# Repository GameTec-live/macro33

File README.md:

# macro33

an attempt at building a small, low profile, portable macro pad...

## Features:

- USB-C
- RP2040 MCU
- QMK
- Hotswap sockets
- Mechanical switches

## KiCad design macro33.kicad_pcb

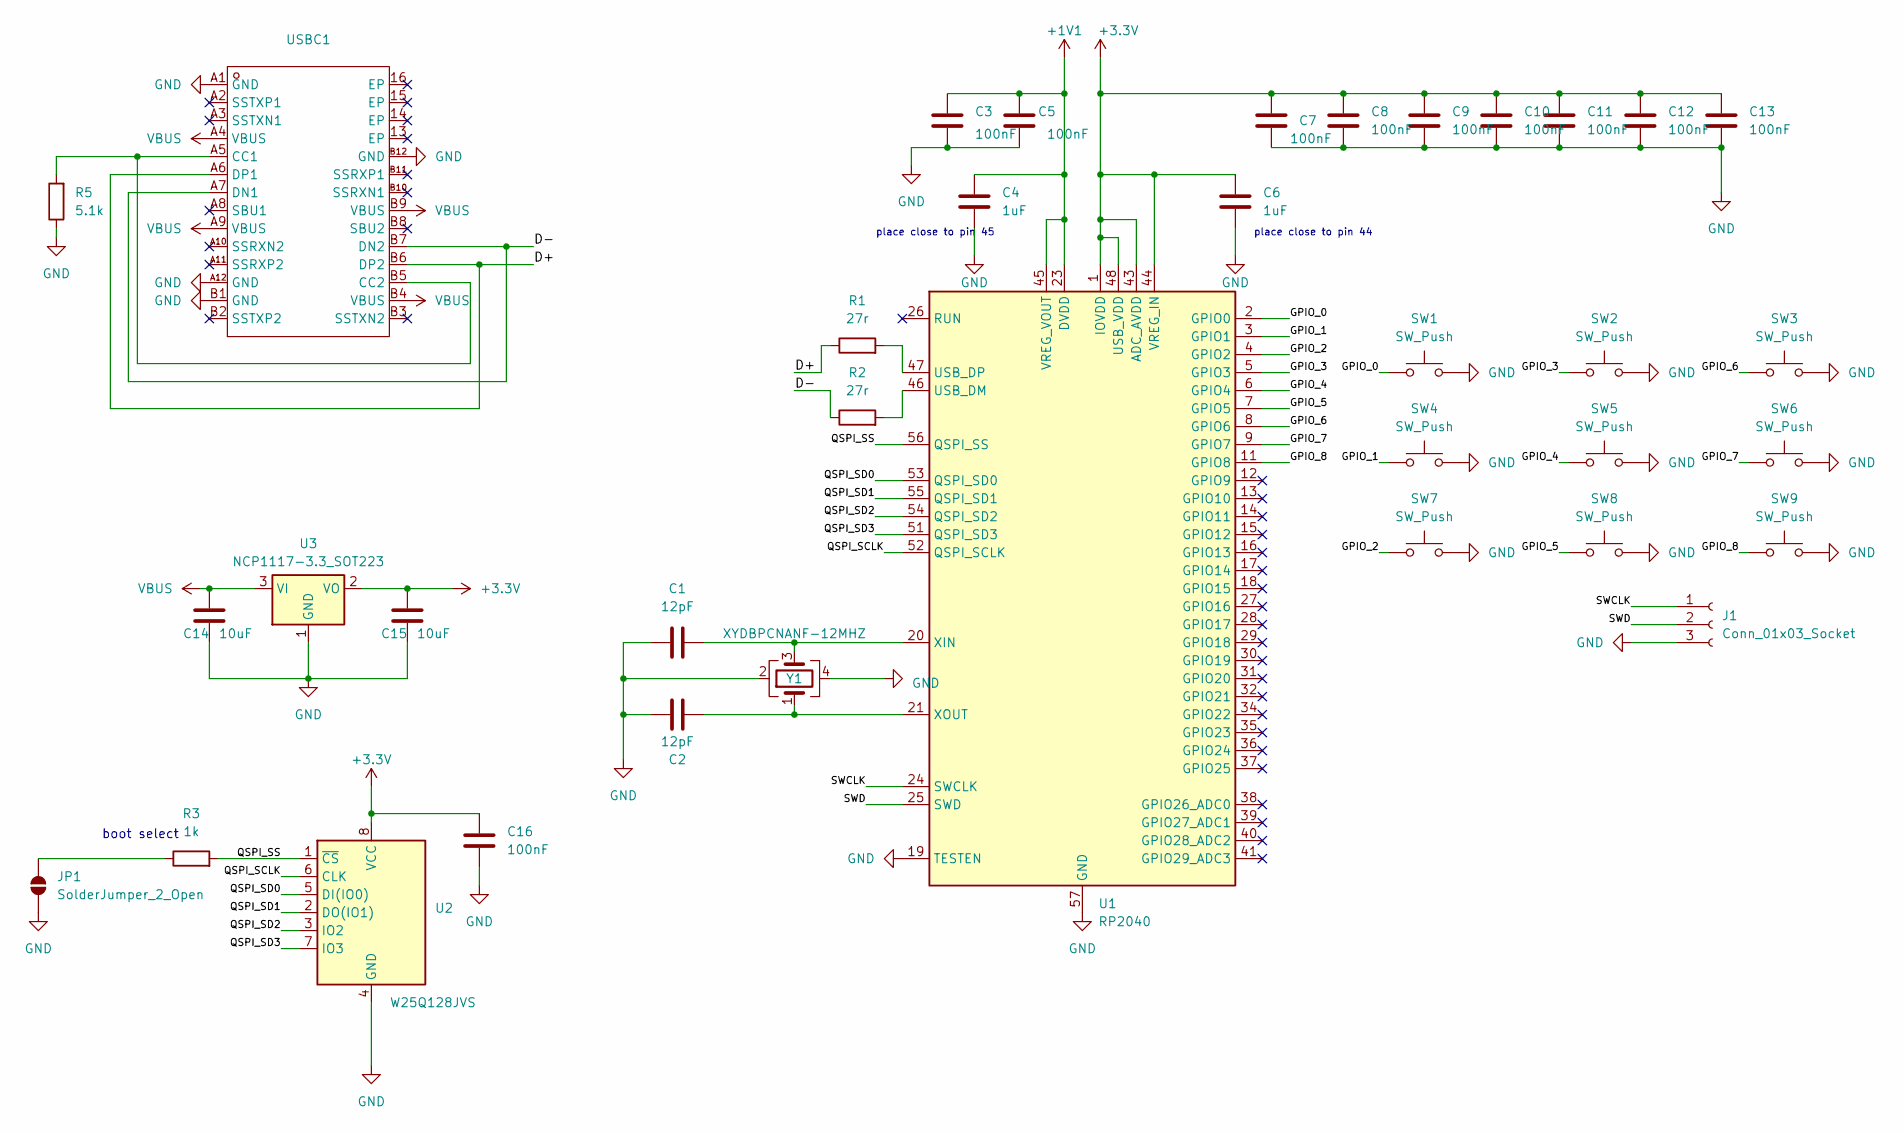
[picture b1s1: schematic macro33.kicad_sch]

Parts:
C1, C2: 12pF; C_0402_1005Metric; LCSC C1547
C3, C5, C7, C8, C9, C10, C11, C12, C13, C16: 100nF; C_0402_1005Metric; LCSC C1525
C4, C6: 1uF; C_0402_1005Metric; LCSC C52923
C14, C15: 10uF; C_1206_3216Metric; LCSC C13585
J1: Conn_01x03_Socket; SWD-Pads
JP1: SolderJumper_2_Open; SolderJumper-2_P1.3mm_Open_TrianglePad1.0x1.5mm
R1, R2: 27r; R_0805_2012Metric; LCSC C17594
R3: 1k; R_0402_1005Metric; LCSC C11702
R5: 5.1k; R_0402_1005Metric; LCSC C25905
SW1, SW2, SW3, SW4, SW5, SW6, SW7, SW8, SW9: SW_Push; CherryMX_MidHeight_Choc_Hotswap_rev5
U1: RP2040; QFN-56-1EP_7x7mm_P0.4mm_EP3.2x3.2mm; LCSC C2040
U2: W25Q128JVS; SOIC-8_5.23x5.23mm_P1.27mm; LCSC C97521
U3: NCP1117-3.3_SOT223; SOT-223-3_TabPin2; LCSC C26537
USBC1: USB-C-SMD_C67380; Manufacturer Part 918-418K2023C40002; LCSC C67380
Y1: XYDBPCNANF-12MHZ; OSC-SMD_4P-L2.5-W2.0-BL; LCSC C521567

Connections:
+1V1: C3.1, C4.1, C5.1, U1.23 (DVDD), U1.45 (VREG_VOUT), U1.50 (DVDD)
+3.3V: C6.1, C7.1, C8.1, C9.1, C10.1, C11.1, C12.1, C13.1, C15.1, C16.1, U1.1 (IOVDD), U1.10 (IOVDD), U1.22 (IOVDD), U1.33 (IOVDD), U1.42 (IOVDD), U1.43 (ADC_AVDD), U1.44 (VREG_IN), U1.48 (USB_VDD), U1.49 (IOVDD), U2.8 (VCC), U3.2 (VO)
/D+: R1.1, USBC1.A6 (DP1), USBC1.B6 (DP2)
/D-: R2.1, USBC1.A7 (DN1), USBC1.B7 (DN2)
/GPIO_0: SW1.1, U1.2 (GPIO0)
/GPIO_1: SW4.1, U1.3 (GPIO1)
/GPIO_2: SW7.1, U1.4 (GPIO2)
/GPIO_3: SW2.1, U1.5 (GPIO3)
/GPIO_4: SW5.1, U1.6 (GPIO4)
/GPIO_5: SW8.1, U1.7 (GPIO5)
/GPIO_6: SW3.1, U1.8 (GPIO6)
/GPIO_7: SW6.1, U1.9 (GPIO7)
/GPIO_8: SW9.1, U1.11 (GPIO8)
/QSPI_SCLK: U1.52 (QSPI_SCLK), U2.6 (CLK)
/QSPI_SD0: U1.53 (QSPI_SD0), U2.5 (DI(IO0))
/QSPI_SD1: U1.55 (QSPI_SD1), U2.2 (DO(IO1))
/QSPI_SD2: U1.54 (QSPI_SD2), U2.3 (IO2)
/QSPI_SD3: U1.51 (QSPI_SD3), U2.7 (IO3)
/QSPI_SS: R3.2, U1.56 (QSPI_SS), U2.1 (~CS)
/SWCLK: J1.1, U1.24 (SWCLK); also elsewhere on the board
/SWD: J1.2, U1.25 (SWD); also elsewhere on the board
GND: C1.1, C2.1, C3.2, C4.2, C5.2, C6.2, C7.2, C8.2, C9.2, C10.2, C11.2, C12.2, C13.2, C14.2, C15.2, C16.2, J1.3, JP1.1 (A), R5.1, SW1.2, SW2.2, SW3.2, SW4.2, SW5.2, SW6.2, SW7.2, SW8.2, SW9.2, U1.19 (TESTEN), U1.57 (GND), U2.4 (GND), U3.1 (GND), USBC1.A1 (GND), USBC1.A12 (GND), USBC1.B1 (GND), USBC1.B12 (GND), Y1.2, Y1.4; also elsewhere on the board
unnamed 22: JP1.2 (B), R3.1; also elsewhere on the board
unnamed: R2.2, U1.46 (USB_DM)
unnamed: R1.2, U1.47 (USB_DP)
unnamed: C1.2, U1.20 (XIN), Y1.3
unnamed: C2.2, U1.21 (XOUT), Y1.1
unnamed: R5.2, USBC1.A5 (CC1), USBC1.B5 (CC2)
VBUS: C14.1, U3.3 (VI), USBC1.A4 (VBUS), USBC1.A9 (VBUS), USBC1.B4 (VBUS), USBC1.B9 (VBUS)

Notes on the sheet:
boot select
place close to pin 45
place close to pin 44

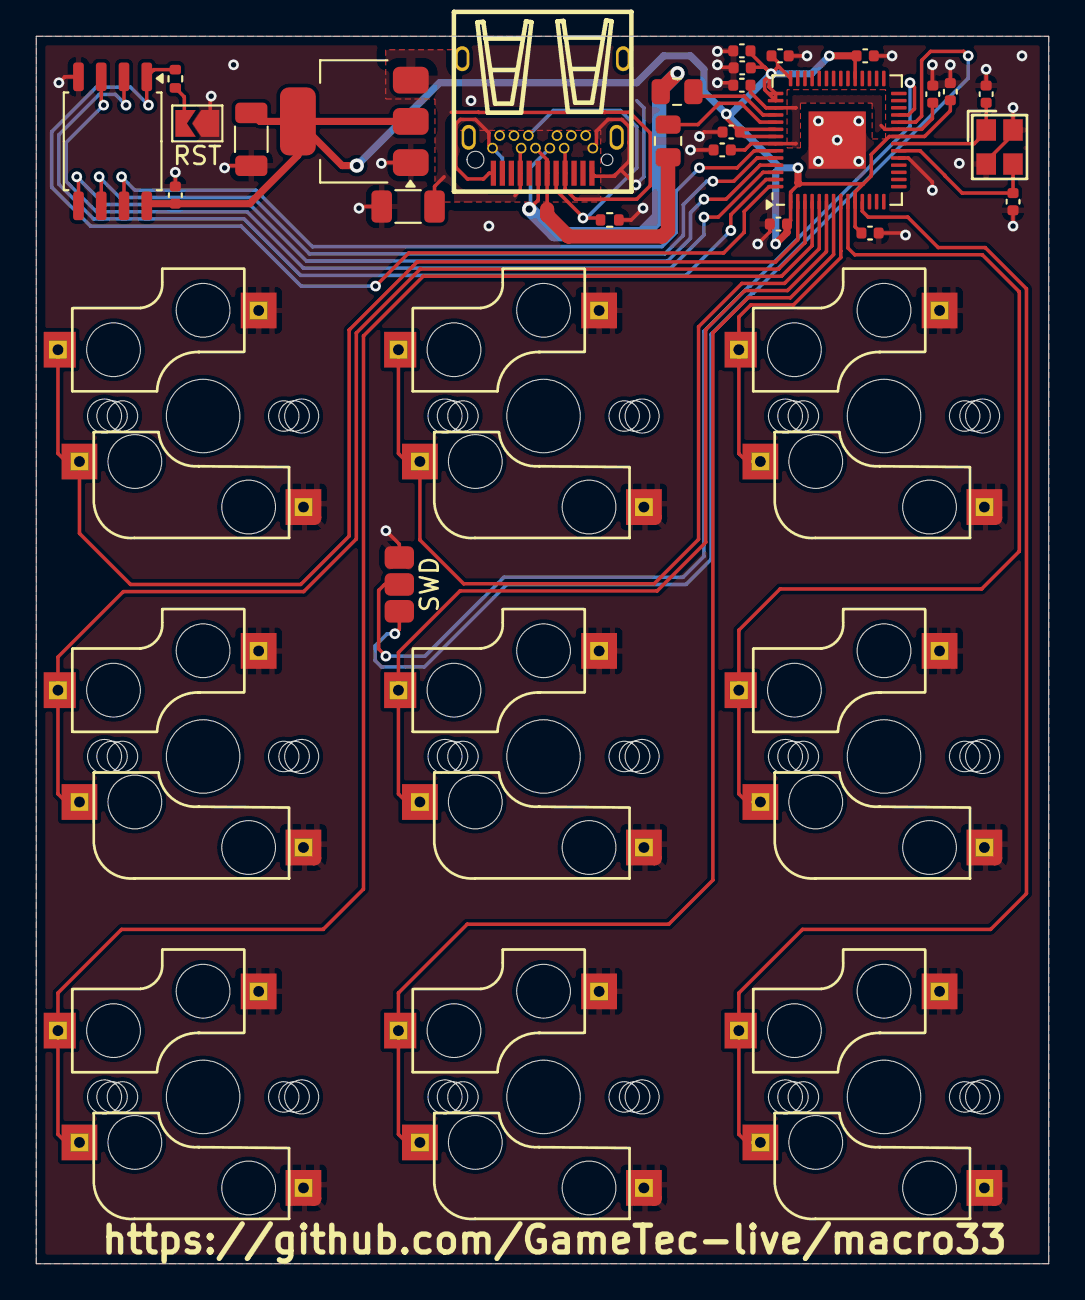
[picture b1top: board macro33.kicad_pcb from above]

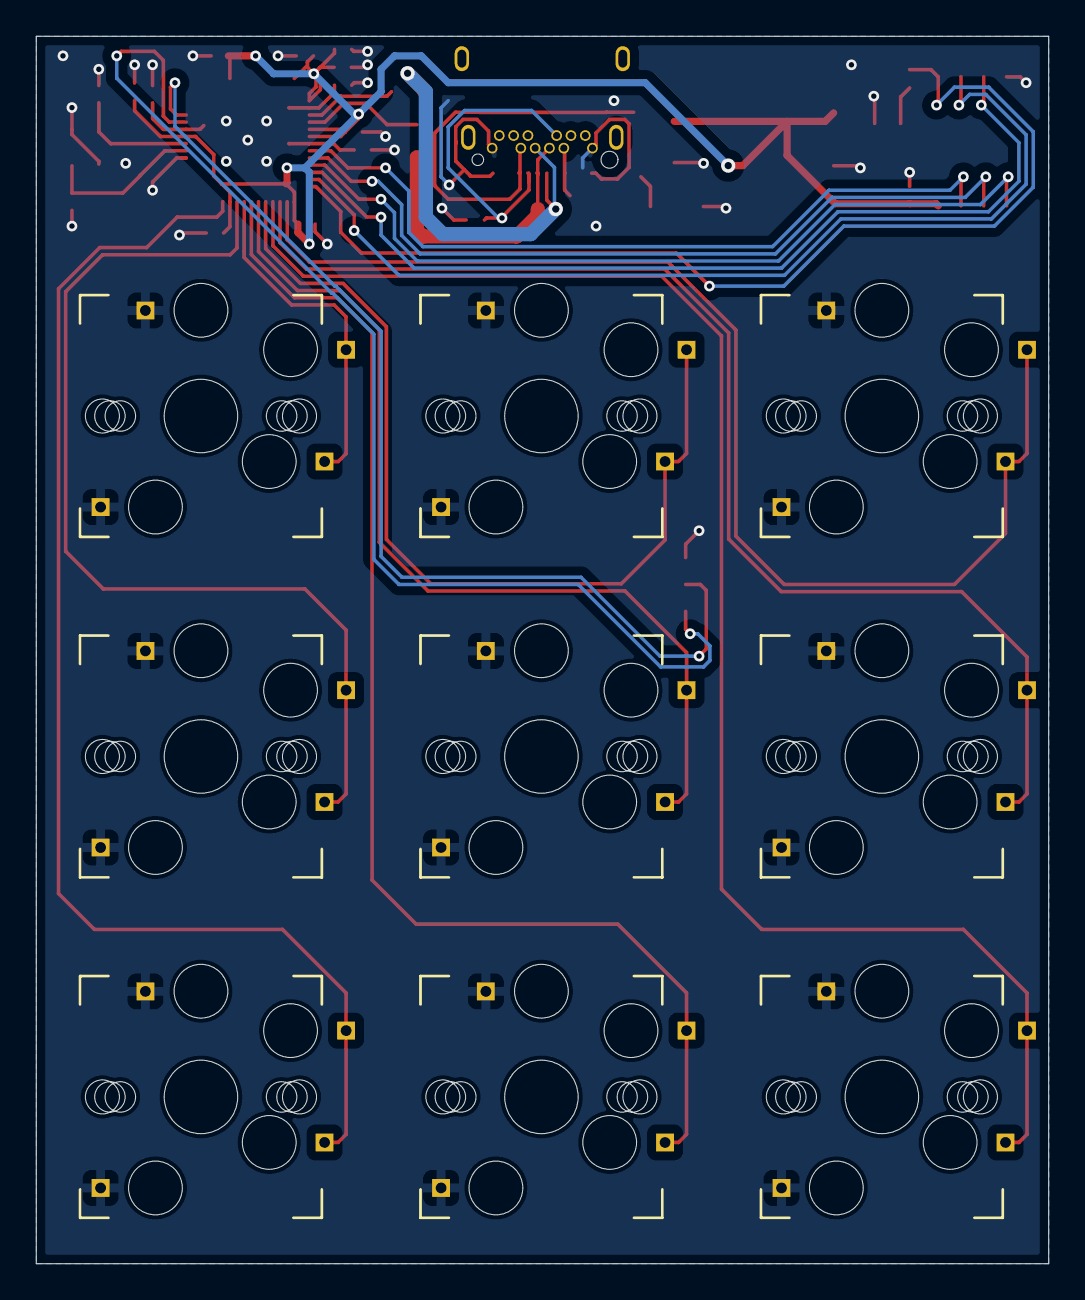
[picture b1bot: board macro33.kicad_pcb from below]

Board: 2 copper layers, 56.5 x 68.5 mm, 36 parts (9 on the bottom side), 29 nets.

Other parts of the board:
RST: SolderJumper_2_Open; SolderJumper-2_P1.3mm_Open_TrianglePad1.0x1.5mm
SWD: Conn_01x03_Socket; SWD-Pads

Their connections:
/SWCLK: SWD.1; also elsewhere on the board
/SWD: SWD.2; also elsewhere on the board
GND: RST.1 (A), SWD.3; also elsewhere on the board
unnamed 22: RST.2 (B); also elsewhere on the board

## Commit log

2025-01-30 feat: kicad proj
2025-01-30 feat: fw
2025-02-10 feat: finished design
2025-02-11 feat: gerbers
2025-02-13 feat: rev2
2025-02-24 feat: edit pinout to conform with layout
2025-10-21 doc: readme

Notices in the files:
macro33.kicad_pcb:
GPLV3 Licensed
